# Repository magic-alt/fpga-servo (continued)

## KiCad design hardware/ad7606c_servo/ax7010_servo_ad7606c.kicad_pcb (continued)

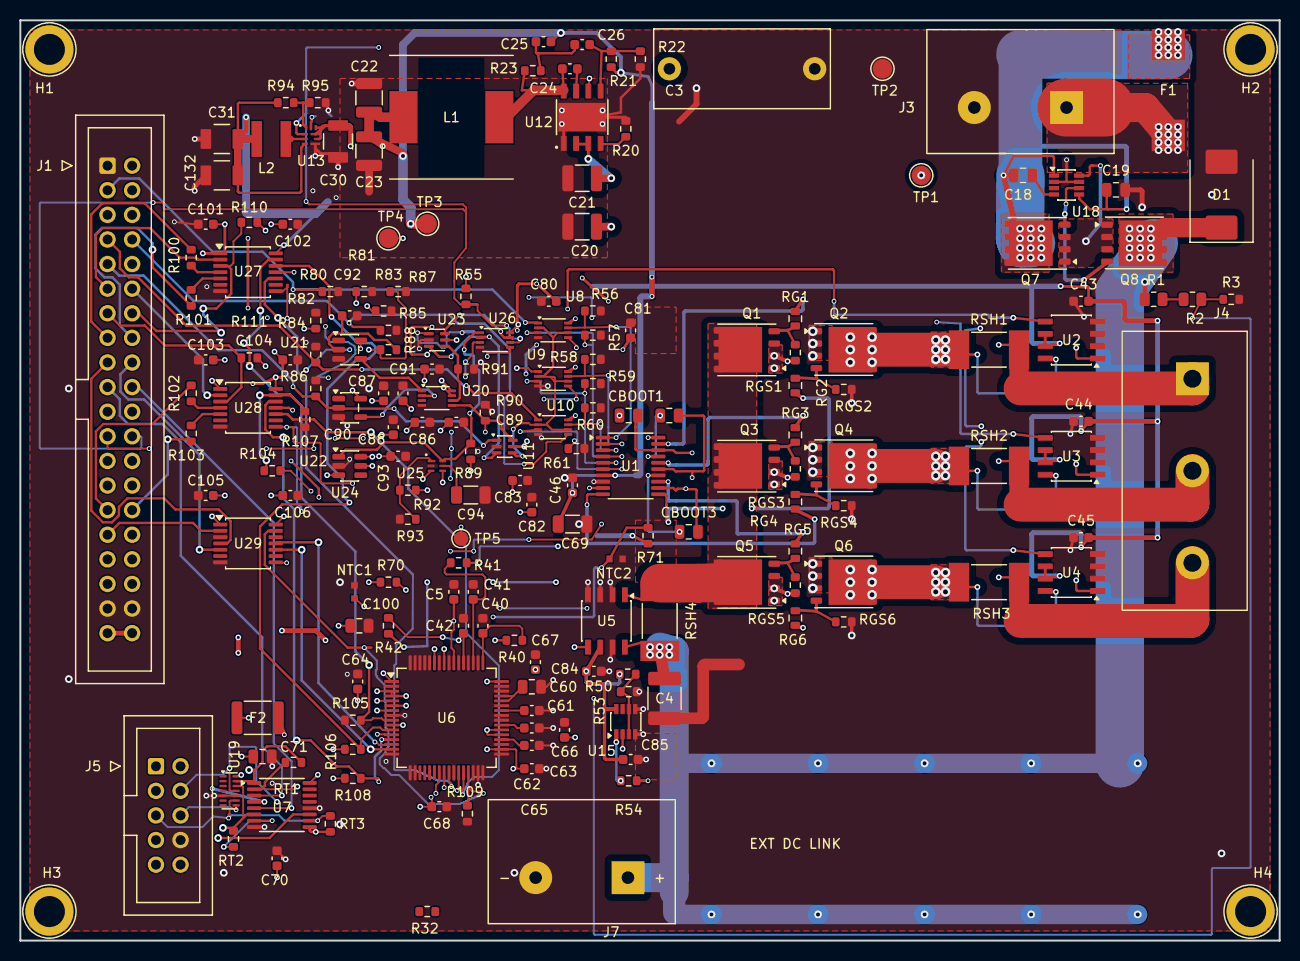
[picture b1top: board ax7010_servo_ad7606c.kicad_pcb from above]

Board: 4 copper layers, 130.0 x 95.0 mm, 185 parts (1 on the bottom side), 121 nets.

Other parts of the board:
H1, H2, H3, H4: M3_HOLE; MountingHole_M3_3.2mm_PTH_Pad5mm

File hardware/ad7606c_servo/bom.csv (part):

Ref,Qty,Value / Part,Manufacturer,MPN,Package,LCSC,Alternative MPN,Alternative LCSC,Status,On_board,DNP
C3,1,1uF,Faratronic,C212E105J6BC000,Capacitor_THT:C_Rect_L18.0mm_W8.0mm_P15.00mm_FKS3_FKP3,C604836,UNQUALIFIED,UNVERIFIED,OPEN,True,False
C4,1,100nF,TDK,C4532C0G2A104JT000N,Capacitor_SMD:C_1812_4532Metric,C342611,FM43N104J101EGG,C42391415,OPEN,True,False
C5,1,10nF,FH(风华),0603B103K101NT,Capacitor_SMD:C_0603_1608Metric,C43253,CL10B103KB8NNNC,C1589,Prototype candidate; OEM reviewed; stock checked 2026-10-10; not production-qualified,True,False
C18,1,220nF,FH(风华),0805B224K500NT,Capacitor_SMD:C_0805_2012Metric,C163697,CL21B224KBFNNNE,C5378,Prototype candidate; OEM reviewed; stock checked 2026-10-10; not production-qualified,True,False
C19,1,100nF,FH(风华),0805B104K101NT,Capacitor_SMD:C_0805_2012Metric,C89258,0805B104K101CT,C77456,Stocked prototype primary and cross-manufacturer alternate; China stock checked2026-10-10; OEM package reviewed; not production-qualified,True,False
C20,1,2.2uF,FH(风华),1210B225K101NT,Capacitor_SMD:C_1210_3225Metric,C42400139,GCJ32DR72A225KA01L,C388903,Prototype candidate; OEM reviewed; stock checked 2026-10-10; not production-qualified,True,False
C21,1,2.2uF,FH(风华),1210B225K101NT,Capacitor_SMD:C_1210_3225Metric,C42400139,GCJ32DR72A225KA01L,C388903,Prototype candidate; OEM reviewed; stock checked 2026-10-10; not production-qualified,True,False
C22,1,22uF,FH(风华),1210B226K250NT,Capacitor_SMD:C_1210_3225Metric,C5204920,CS3225X7R226K250NRL,C2918511,Prototype candidate; OEM reviewed; stock checked 2026-10-10; not production-qualified,True,False
C23,1,22uF,FH(风华),1210B226K250NT,Capacitor_SMD:C_1210_3225Metric,C5204920,CS3225X7R226K250NRL,C2918511,Prototype candidate; OEM reviewed; stock checked 2026-10-10; not production-qualified,True,False
C24,1,2.2nF,FH(风华),0603B222J500NT,Capacitor_SMD:C_0603_1608Metric,C60328,CL10B222KB8NNNC,C16033,Prototype candidate; OEM reviewed; stock checked 2026-10-10; not production-qualified,True,False
C25,1,3.3nF,Murata,GRM1885C1H332JA01D,Capacitor_SMD:C_0603_1608Metric,C77036,UNQUALIFIED,UNVERIFIED,12V total 1A ECO; exact primary required; procurement and bench OPEN,True,False
C26,1,56pF,FH(风华),0603CG560J500NT,Capacitor_SMD:C_0603_1608Metric,C1676,CL10C560JB81PNC,C472797,Prototype candidate; OEM reviewed; stock checked 2026-10-10; not production-qualified,True,False
C30,1,22uF,Murata,GRM32ER71E226KE15L,fpga-servo:Murata_GRM32_1210,C21397,UNQUALIFIED,UNVERIFIED,Exact primary; OEM combined DC/AC typical model with engineering reserves; incoming effective-C and startup/loop bench OPEN; no alternate qualification,True,False
C31,1,22uF,Murata,GRM32ER71E226KE15L,fpga-servo:Murata_GRM32_1210,C21397,UNQUALIFIED,UNVERIFIED,Exact primary; OEM combined DC/AC typical model with engineering reserves; incoming effective-C and startup/loop bench OPEN; no alternate qualification,True,False
C40,1,1nF,FH(风华),0603CG102J101NT,Capacitor_SMD:C_0603_1608Metric,C88489,CL10C102JB8NNNC,C163508,Prototype candidate; OEM reviewed; stock checked 2026-10-10; not production-qualified,True,False
C41,1,1nF,FH(风华),0603CG102J101NT,Capacitor_SMD:C_0603_1608Metric,C88489,CL10C102JB8NNNC,C163508,Prototype candidate; OEM reviewed; stock checked 2026-10-10; not production-qualified,True,False
C42,1,1nF,FH(风华),0603CG102J101NT,Capacitor_SMD:C_0603_1608Metric,C88489,CL10C102JB8NNNC,C163508,Prototype candidate; OEM reviewed; stock checked 2026-10-10; not production-qualified,True,False
C43,1,100nF,FH(风华),0603B104K500NT,Capacitor_SMD:C_0603_1608Metric,C30926,CL10B104KB8NNNC,C1591,Prototype candidate; OEM reviewed; stock checked 2026-10-10; not production-qualified,True,False
C44,1,100nF,FH(风华),0603B104K500NT,Capacitor_SMD:C_0603_1608Metric,C30926,CL10B104KB8NNNC,C1591,Prototype candidate; OEM reviewed; stock checked 2026-10-10; not production-qualified,True,False
C45,1,100nF,FH(风华),0603B104K500NT,Capacitor_SMD:C_0603_1608Metric,C30926,CL10B104KB8NNNC,C1591,Prototype candidate; OEM reviewed; stock checked 2026-10-10; not production-qualified,True,False
C46,1,100nF,FH(风华),0603B104K500NT,Capacitor_SMD:C_0603_1608Metric,C30926,CL10B104KB8NNNC,C1591,Prototype candidate; OEM reviewed; stock checked 2026-10-10; not production-qualified,True,False
C60,1,10uF,Chinocera(华瓷),HGC0805R7106K250NSLJ,Capacitor_SMD:C_0805_2012Metric,C33546010,FCC0805B106K250FT,C54619707,Prototype candidate; OEM reviewed; stock checked 2026-10-10; not production-qualified,True,False
C61,1,100nF,FH(风华),0603B104K500NT,Capacitor_SMD:C_0603_1608Metric,C30926,CL10B104KB8NNNC,C1591,Prototype candidate; OEM reviewed; stock checked 2026-10-10; not production-qualified,True,False
C62,1,1uF,FH(风华),0603B105K250NT,Capacitor_SMD:C_0603_1608Metric,C59302,CL10B105KA8NNNC,C29936,Prototype candidate; OEM reviewed; stock checked 2026-10-10; not production-qualified,True,False
C63,1,1uF,FH(风华),0603B105K250NT,Capacitor_SMD:C_0603_1608Metric,C59302,CL10B105KA8NNNC,C29936,Prototype candidate; OEM reviewed; stock checked 2026-10-10; not production-qualified,True,False
C64,1,100nF,FH(风华),0603B104K500NT,Capacitor_SMD:C_0603_1608Metric,C30926,CL10B104KB8NNNC,C1591,Prototype candidate; OEM reviewed; stock checked 2026-10-10; not production-qualified,True,False
C65,1,100nF,FH(风华),0603B104K500NT,Capacitor_SMD:C_0603_1608Metric,C30926,CL10B104KB8NNNC,C1591,Prototype candidate; OEM reviewed; stock checked 2026-10-10; not production-qualified,True,False
C66,1,100nF,FH(风华),0603B104K500NT,Capacitor_SMD:C_0603_1608Metric,C30926,CL10B104KB8NNNC,C1591,Prototype candidate; OEM reviewed; stock checked 2026-10-10; not production-qualified,True,False
C67,1,100nF,FH(风华),0603B104K500NT,Capacitor_SMD:C_0603_1608Metric,C30926,CL10B104KB8NNNC,C1591,Prototype candidate; OEM reviewed; stock checked 2026-10-10; not production-qualified,True,False
C68,1,100nF,FH(风华),0603B104K500NT,Capacitor_SMD:C_0603_1608Metric,C30926,CL10B104KB8NNNC,C1591,Prototype candidate; OEM reviewed; stock checked 2026-10-10; not production-qualified,True,False
C69,1,10uF,HRE(芯声),CGA1206X7R106K250NT,Capacitor_SMD:C_1206_3216Metric,C6119987,CC1206KKX7R8BB106,C70462,Prototype candidate; OEM reviewed; stock checked 2026-10-10; not production-qualified,True,False
C70,1,100nF,FH(风华),0603B104K500NT,Capacitor_SMD:C_0603_1608Metric,C30926,CL10B104KB8NNNC,C1591,Prototype candidate; OEM reviewed; stock checked 2026-10-10; not production-qualified,True,False
C71,1,4.7uF,HRE(芯声),CGA0805X7R475K250MT,Capacitor_SMD:C_0805_2012Metric,C6119942,CL21B475KOFNNNE,C107365,Prototype candidate; OEM reviewed; stock checked 2026-10-10; not production-qualified,True,False
C80,1,100nF,FH(风华),0603B104K500NT,Capacitor_SMD:C_0603_1608Metric,C30926,CL10B104KB8NNNC,C1591,Prototype candidate; OEM reviewed; stock checked 2026-10-10; not production-qualified,True,False
C81,1,100nF,FH(风华),0603B104K500NT,Capacitor_SMD:C_0603_1608Metric,C30926,CL10B104KB8NNNC,C1591,Prototype candidate; OEM reviewed; stock checked 2026-10-10; not production-qualified,True,False
C82,1,100nF,FH(风华),0603B104K500NT,Capacitor_SMD:C_0603_1608Metric,C30926,CL10B104KB8NNNC,C1591,Prototype candidate; OEM reviewed; stock checked 2026-10-10; not production-qualified,True,False
C83,1,100nF,FH(风华),0603B104K500NT,Capacitor_SMD:C_0603_1608Metric,C30926,CL10B104KB8NNNC,C1591,Prototype candidate; OEM reviewed; stock checked 2026-10-10; not production-qualified,True,False
C84,1,100nF,FH(风华),0603B104K500NT,Capacitor_SMD:C_0603_1608Metric,C30926,CL10B104KB8NNNC,C1591,Prototype candidate; OEM reviewed; stock checked 2026-10-10; not production-qualified,True,False
C85,1,100nF,FH(风华),0603B104K500NT,Capacitor_SMD:C_0603_1608Metric,C30926,CL10B104KB8NNNC,C1591,Prototype candidate; OEM reviewed; stock checked 2026-10-10; not production-qualified,True,False
C86,1,100nF,FH(风华),0603B104K500NT,Capacitor_SMD:C_0603_1608Metric,C30926,CL10B104KB8NNNC,C1591,Prototype candidate; OEM reviewed; stock checked 2026-10-10; not production-qualified,True,False
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
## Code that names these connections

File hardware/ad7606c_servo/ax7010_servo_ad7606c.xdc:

# AX7010 Servo Drive Rev.A
# Confirmed user hardware: AX7010 2022, active PL_A=J10. PL_B=J11 optional.
# Pin mapping checked against manufacturer schematic sheets 5/15; no pin changes.
# Only J10/PL_A is wired by this daughterboard. J11/PL_B assignments below
# are reference-only comments, NOT implementable net connections.
# All user PL I/O here is 3.3 V LVCMOS.

# PL_A / J10
set_property PACKAGE_PIN W19 [get_ports PWM_UH];        set_property IOSTANDARD LVCMOS33 [get_ports PWM_UH]
set_property PACKAGE_PIN W18 [get_ports PWM_UL];        set_property IOSTANDARD LVCMOS33 [get_ports PWM_UL]
set_property PACKAGE_PIN R14 [get_ports PWM_VH];        set_property IOSTANDARD LVCMOS33 [get_ports PWM_VH]
set_property PACKAGE_PIN P14 [get_ports PWM_VL];        set_property IOSTANDARD LVCMOS33 [get_ports PWM_VL]
set_property PACKAGE_PIN Y17 [get_ports PWM_WH];        set_property IOSTANDARD LVCMOS33 [get_ports PWM_WH]
set_property PACKAGE_PIN Y16 [get_ports PWM_WL];        set_property IOSTANDARD LVCMOS33 [get_ports PWM_WL]
set_property PACKAGE_PIN W15 [get_ports GATE_EN];       set_property IOSTANDARD LVCMOS33 [get_ports GATE_EN]
set_property PACKAGE_PIN V15 [get_ports FAULT_CLEAR];   set_property IOSTANDARD LVCMOS33 [get_ports FAULT_CLEAR]
set_property PACKAGE_PIN Y14 [get_ports ADC_CONVST];    set_property IOSTANDARD LVCMOS33 [get_ports ADC_CONVST]
set_property PACKAGE_PIN W14 [get_ports ADC_SCLK];      set_property IOSTANDARD LVCMOS33 [get_ports ADC_SCLK]
set_property PACKAGE_PIN P18 [get_ports ADC_CS_N];      set_property IOSTANDARD LVCMOS33 [get_ports ADC_CS_N]
set_property PACKAGE_PIN N17 [get_ports ADC_RESET];     set_property IOSTANDARD LVCMOS33 [get_ports ADC_RESET]
set_property PACKAGE_PIN U15 [get_ports ADC_DOUTA];     set_property IOSTANDARD LVCMOS33 [get_ports ADC_DOUTA]
set_property PACKAGE_PIN U14 [get_ports ADC_DOUTB];     set_property IOSTANDARD LVCMOS33 [get_ports ADC_DOUTB]
set_property PACKAGE_PIN P16 [get_ports ADC_BUSY];      set_property IOSTANDARD LVCMOS33 [get_ports ADC_BUSY]
set_property PACKAGE_PIN P15 [get_ports ADC_FRSTDATA];  set_property IOSTANDARD LVCMOS33 [get_ports ADC_FRSTDATA]
set_property PACKAGE_PIN U17 [get_ports ENC_A];         set_property IOSTANDARD LVCMOS33 [get_ports ENC_A]
set_property PACKAGE_PIN T16 [get_ports ENC_B];         set_property IOSTANDARD LVCMOS33 [get_ports ENC_B]
set_property PACKAGE_PIN V18 [get_ports ENC_Z];         set_property IOSTANDARD LVCMOS33 [get_ports ENC_Z]
set_property PACKAGE_PIN V17 [get_ports ENC_FAULT_N];   set_property IOSTANDARD LVCMOS33 [get_ports ENC_FAULT_N]
set_property PACKAGE_PIN T15 [get_ports OCP_N];         set_property IOSTANDARD LVCMOS33 [get_ports OCP_N]
set_property PACKAGE_PIN T14 [get_ports PWR_GOOD];      set_property IOSTANDARD LVCMOS33 [get_ports PWR_GOOD]
set_property PACKAGE_PIN V13 [get_ports AUX_IN0];       set_property IOSTANDARD LVCMOS33 [get_ports AUX_IN0]
set_property PACKAGE_PIN U13 [get_ports AUX_IN1];       set_property IOSTANDARD LVCMOS33 [get_ports AUX_IN1]
set_property PACKAGE_PIN W13 [get_ports AUX_OUT0];      set_property IOSTANDARD LVCMOS33 [get_ports AUX_OUT0]
set_property PACKAGE_PIN V12 [get_ports AUX_OUT1];      set_property IOSTANDARD LVCMOS33 [get_ports AUX_OUT1]

# PL_B / J11 - optional ADC parallel + debug
# set_property PACKAGE_PIN F17 [get_ports {ADC_DB[0]}];  set_property IOSTANDARD LVCMOS33 [get_ports {ADC_DB[0]}]
# set_property PACKAGE_PIN F16 [get_ports {ADC_DB[1]}];  set_property IOSTANDARD LVCMOS33 [get_ports {ADC_DB[1]}]
# set_property PACKAGE_PIN F20 [get_ports {ADC_DB[2]}];  set_property IOSTANDARD LVCMOS33 [get_ports {ADC_DB[2]}]
# set_property PACKAGE_PIN F19 [get_ports {ADC_DB[3]}];  set_property IOSTANDARD LVCMOS33 [get_ports {ADC_DB[3]}]
# set_property PACKAGE_PIN G20 [get_ports {ADC_DB[4]}];  set_property IOSTANDARD LVCMOS33 [get_ports {ADC_DB[4]}]
# set_property PACKAGE_PIN G19 [get_ports {ADC_DB[5]}];  set_property IOSTANDARD LVCMOS33 [get_ports {ADC_DB[5]}]
# set_property PACKAGE_PIN H18 [get_ports {ADC_DB[6]}];  set_property IOSTANDARD LVCMOS33 [get_ports {ADC_DB[6]}]
# set_property PACKAGE_PIN J18 [get_ports {ADC_DB[7]}];  set_property IOSTANDARD LVCMOS33 [get_ports {ADC_DB[7]}]
# set_property PACKAGE_PIN L20 [get_ports {ADC_DB[8]}];  set_property IOSTANDARD LVCMOS33 [get_ports {ADC_DB[8]}]
# set_property PACKAGE_PIN L19 [get_ports {ADC_DB[9]}];  set_property IOSTANDARD LVCMOS33 [get_ports {ADC_DB[9]}]
# set_property PACKAGE_PIN M20 [get_ports {ADC_DB[10]}]; set_property IOSTANDARD LVCMOS33 [get_ports {ADC_DB[10]}]
# set_property PACKAGE_PIN M19 [get_ports {ADC_DB[11]}]; set_property IOSTANDARD LVCMOS33 [get_ports {ADC_DB[11]}]
# set_property PACKAGE_PIN K18 [get_ports {ADC_DB[12]}]; set_property IOSTANDARD LVCMOS33 [get_ports {ADC_DB[12]}]
# set_property PACKAGE_PIN K17 [get_ports {ADC_DB[13]}]; set_property IOSTANDARD LVCMOS33 [get_ports {ADC_DB[13]}]
# set_property PACKAGE_PIN J19 [get_ports {ADC_DB[14]}]; set_property IOSTANDARD LVCMOS33 [get_ports {ADC_DB[14]}]
# set_property PACKAGE_PIN K19 [get_ports {ADC_DB[15]}]; set_property IOSTANDARD LVCMOS33 [get_ports {ADC_DB[15]}]
# set_property PACKAGE_PIN H20 [get_ports ADC_RD_N];      set_property IOSTANDARD LVCMOS33 [get_ports ADC_RD_N]
# set_property PACKAGE_PIN J20 [get_ports ADC_BYTE_SEL];  set_property IOSTANDARD LVCMOS33 [get_ports ADC_BYTE_SEL]
# set_property PACKAGE_PIN L17 [get_ports ADC_RANGE];     set_property IOSTANDARD LVCMOS33 [get_ports ADC_RANGE]
# set_property PACKAGE_PIN L16 [get_ports ADC_OS0];       set_property IOSTANDARD LVCMOS33 [get_ports ADC_OS0]
# set_property PACKAGE_PIN M18 [get_ports ADC_OS1];       set_property IOSTANDARD LVCMOS33 [get_ports ADC_OS1]
# set_property PACKAGE_PIN M17 [get_ports ADC_OS2];       set_property IOSTANDARD LVCMOS33 [get_ports ADC_OS2]
# set_property PACKAGE_PIN D20 [get_ports ADC_STBY];      set_property IOSTANDARD LVCMOS33 [get_ports ADC_STBY]
# set_property PACKAGE_PIN D19 [get_ports ADC_PAR_SER];   set_property IOSTANDARD LVCMOS33 [get_ports ADC_PAR_SER]
# set_property PACKAGE_PIN E19 [get_ports HALL_U];        set_property IOSTANDARD LVCMOS33 [get_ports HALL_U]
# set_property PACKAGE_PIN E18 [get_ports HALL_V];        set_property IOSTANDARD LVCMOS33 [get_ports HALL_V]
# set_property PACKAGE_PIN G18 [get_ports HALL_W];        set_property IOSTANDARD LVCMOS33 [get_ports HALL_W]
# set_property PACKAGE_PIN G17 [get_ports BRAKE_OUT];     set_property IOSTANDARD LVCMOS33 [get_ports BRAKE_OUT]
# set_property PACKAGE_PIN H17 [get_ports EXT_FAULT_N];   set_property IOSTANDARD LVCMOS33 [get_ports EXT_FAULT_N]
# set_property PACKAGE_PIN H16 [get_ports TEST_TRIG];     set_property IOSTANDARD LVCMOS33 [get_ports TEST_TRIG]

# AD7606C independent schematic only; Vivado STA and physical J10 validation OPEN.
set_property PACKAGE_PIN U12 [get_ports ADC_DOUTC]; set_property IOSTANDARD LVCMOS33 [get_ports ADC_DOUTC]
set_property PACKAGE_PIN T12 [get_ports ADC_DOUTD]; set_property IOSTANDARD LVCMOS33 [get_ports ADC_DOUTD]
set_property PACKAGE_PIN T10 [get_ports ADC_SDI]; set_property IOSTANDARD LVCMOS33 [get_ports ADC_SDI]

# FITTED AD7606C / TXU0204 timing review, 2026-10-19 (NOT implemented STA).
# ADC DOUT changes after SCLK RISING; reference capture is the following FALLING edge.
# Full-temp raw loop: SCLK TXU 9ns + ADC 15.7ns + DOUT TXU 10ns = 34.7ns.
# At 20MHz/50% duty the 25ns half-cycle has -9.7ns BEFORE board/RC/load/FPGA.
# Start at 5MHz: 100ns half-cycle leaves 65.3ns raw, not a qualified margin.
# Datasheet translator load is 5pF/10kohm; actual loading must be bounded.
# Future RTL must constrain generated-clock duty, return delay, setup AND hold,
# first CS/MSB, SDI and BUSY/FRSTDATA. Do not copy pin-only XDC as timing signoff.
# Faster operation needs deliberate capture phase/architecture and real STA/bench.
